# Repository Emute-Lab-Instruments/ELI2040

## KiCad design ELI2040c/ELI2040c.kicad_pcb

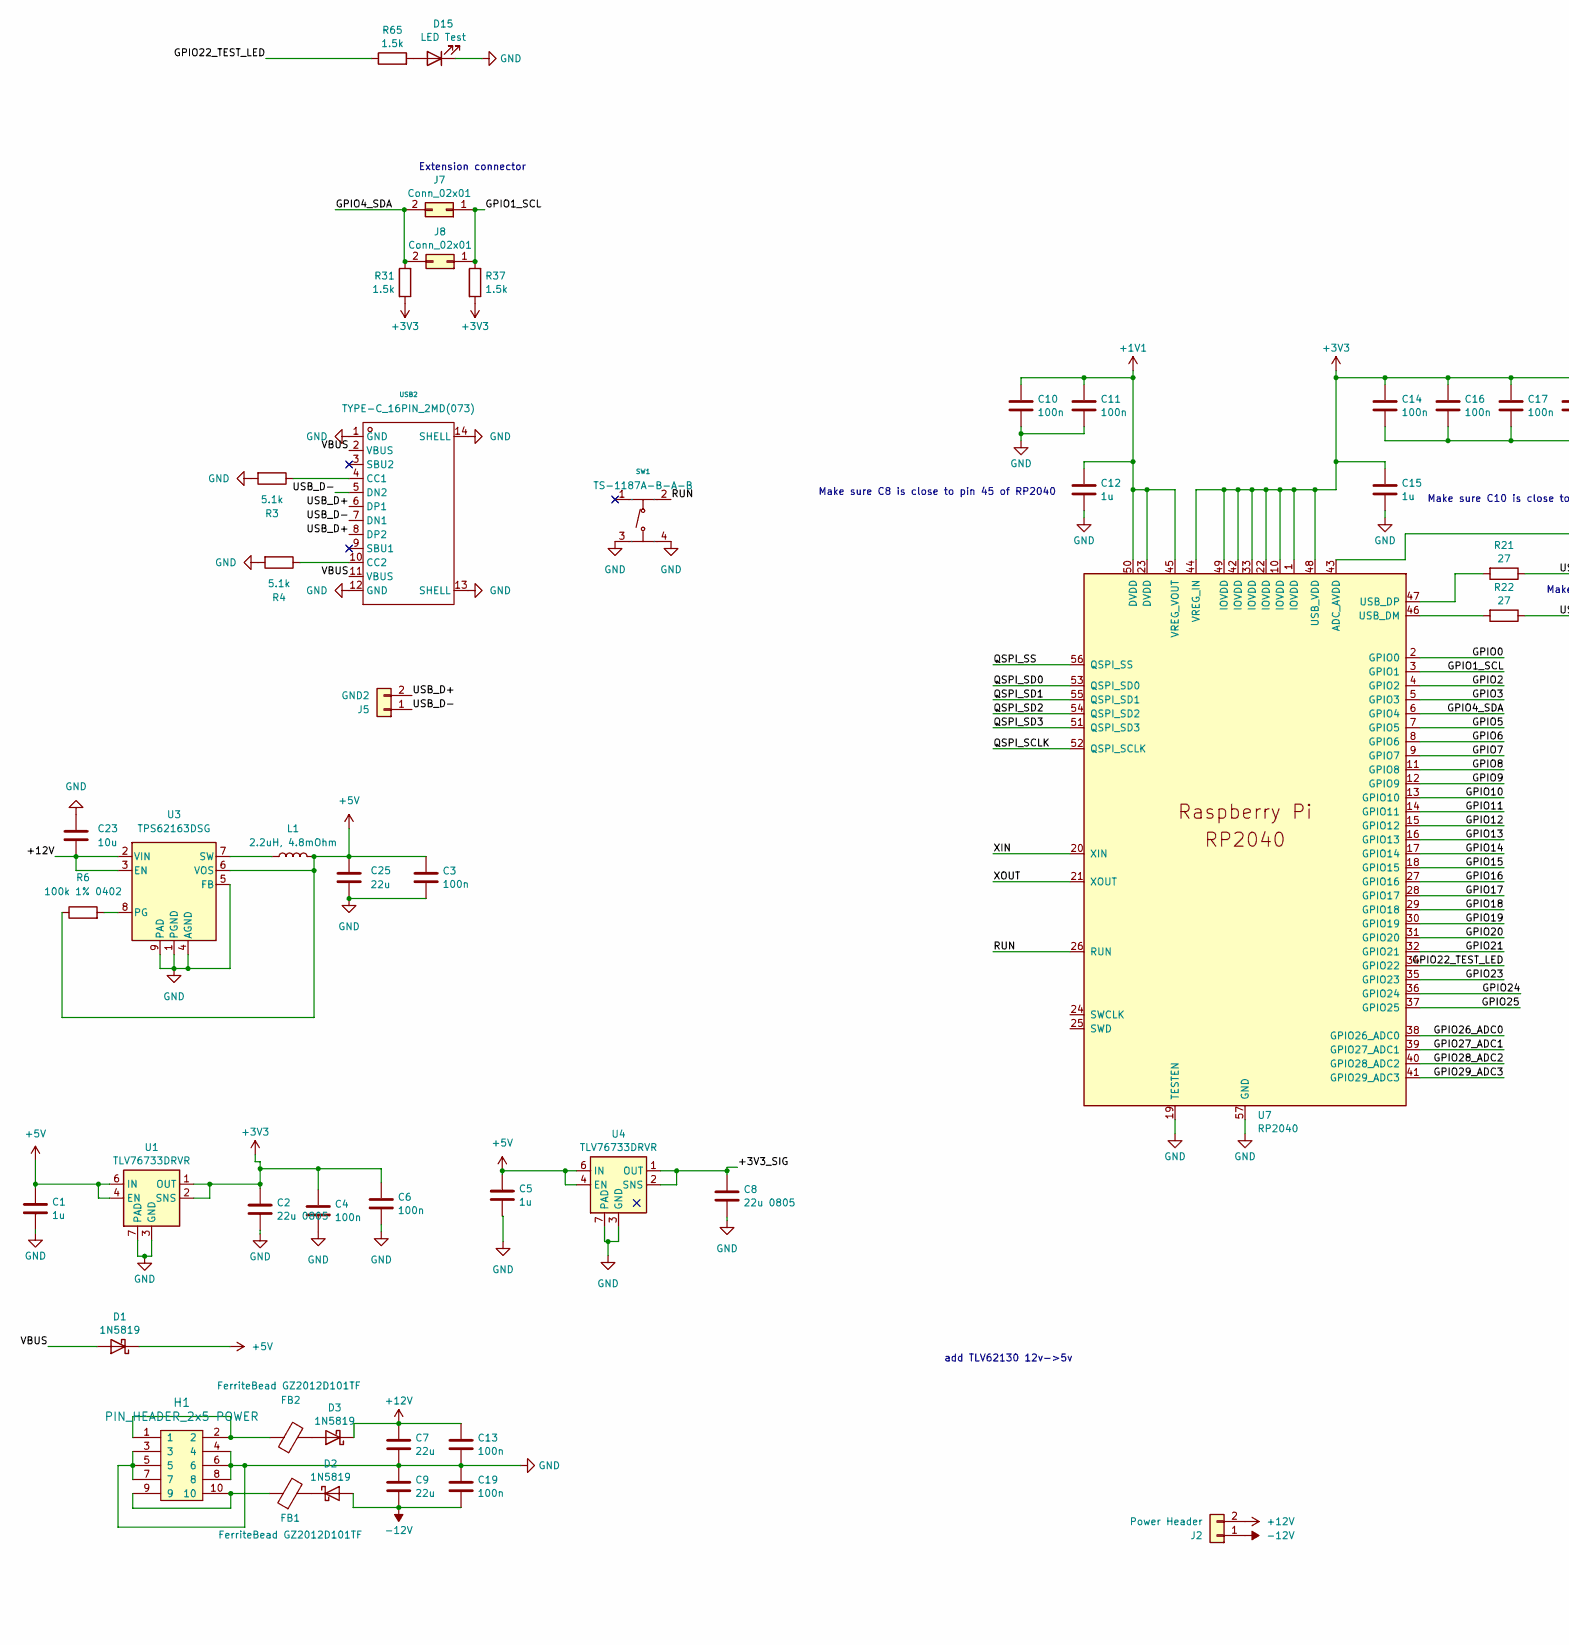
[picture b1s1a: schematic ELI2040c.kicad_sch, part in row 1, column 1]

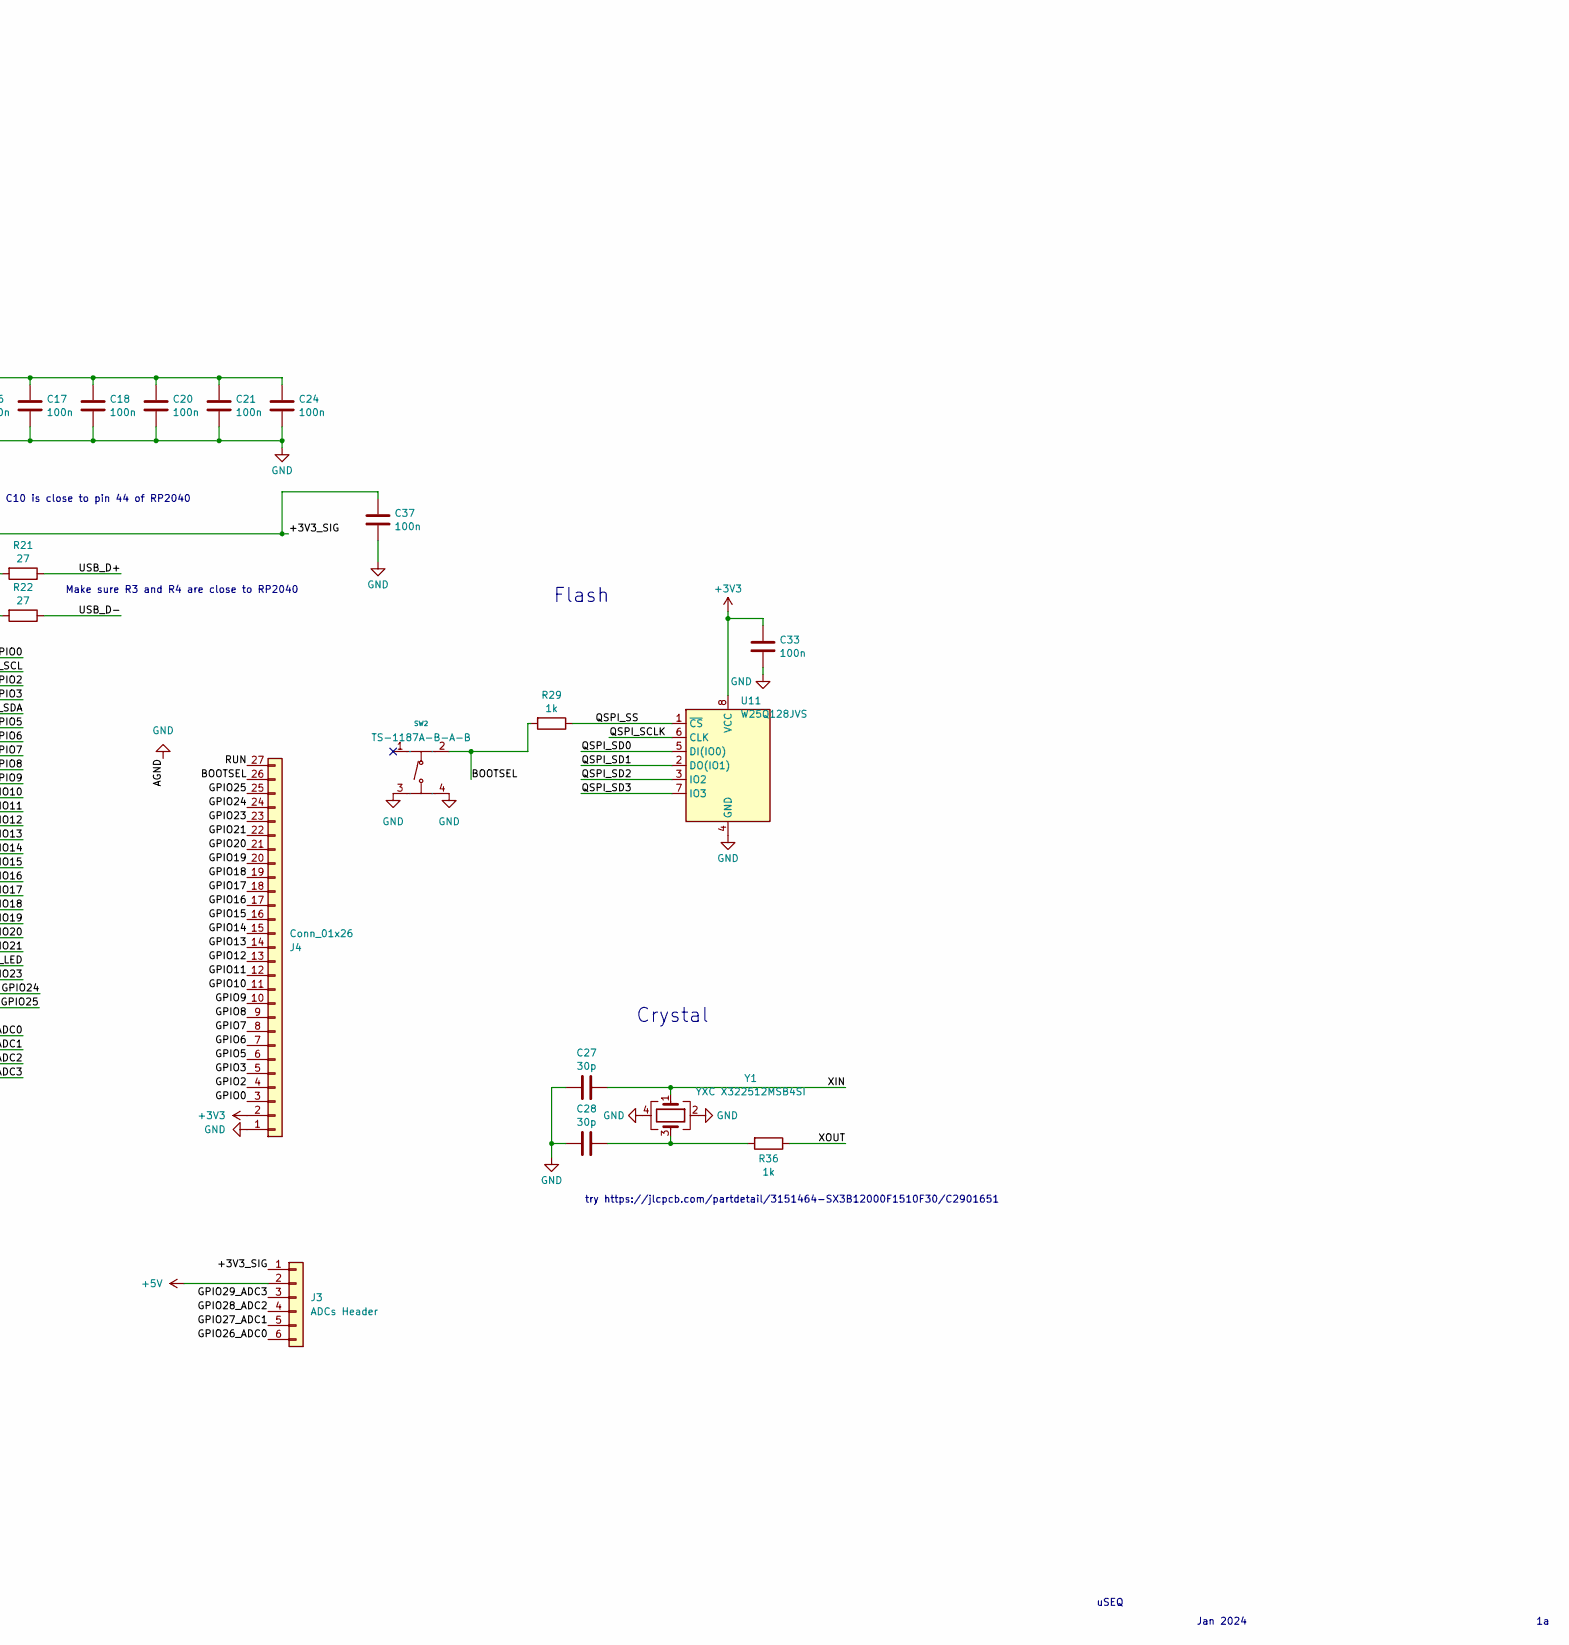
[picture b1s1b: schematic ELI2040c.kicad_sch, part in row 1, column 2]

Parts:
C1, C5: 1u; C_0603_1608Metric_Pad1.08x0.95mm_HandSolder
C2, C8: 22u 0805; C_0805_2012Metric_Pad1.18x1.45mm_HandSolder
C3, C13, C19: 100n; C_0603_1608Metric
C4, C6, C10, C11, C14, C16, C17, C18, C20, C21, C24, C33, C37: 100n; C_0402_1005Metric
C7, C9, C25: 22u; C_0805_2012Metric
C12, C15: 1u; C_0402_1005Metric
C23: 10u; C_0603_1608Metric
C27, C28: 30p; C_0402_1005Metric
D1, D2, D3: 1N5819; D_SOD-323
D15: LED Test; LED_0603_1608Metric
FB1, FB2: FerriteBead GZ2012D101TF; R_0805_2012Metric
H1: PIN_HEADER_2x5 POWER; PinHeader_2x05_P2.54mm_Vertical_SMD
J2: Power Header; PinHeader_1x02_P2.54mm_Vertical
J3: ADCs Header; PinHeader_1x06_P2.54mm_Vertical
J4: Conn_01x26; PinHeader_1x27_P2.54mm_Vertical
J5: GND2; PinHeader_1x02_P2.54mm_Vertical
J7, J8: Conn_02x01; PinHeader_1x02_P2.54mm_Vertical
L1: 2.2uH, 4.8mOhm; L_Sunlord_SWPA4020S
R3, R4: 5.1k; R_0402_1005Metric
R6: 100k 1% 0402; R_0402_1005Metric
R21, R22: 27; C_0402_1005Metric
R29: 1k; R_0402_1005Metric
R31, R37, R65: 1.5k; R_0603_1608Metric
R36: 1k; R_0603_1608Metric
SW1, SW2: TS-1187A-B-A-B; SW-SMD_4P-L5.1-W5.1-P3.70-LS6.5-TL-2; Manufacturer Part TS-1187A-B-A-B; LCSC Part Name 5.1*5.1*1.5mm 立贴 轻触开关
U1, U4: TLV76733DRVR; WSON-6-1EP_2x2mm_P0.65mm_EP1x1.6mm_ThermalVias
U3: TPS62163DSG; WSON-8-1EP_2x2mm_P0.5mm_EP0.9x1.6mm_ThermalVias
U7: RP2040; RP2040-QFN-56
U11: W25Q128JVS; SOIC-8_5.23x5.23mm_P1.27mm
USB2: TYPE-C_16PIN_2MD(073); USB-C-SMD_TYPE-C-6PIN-2MD-073
Y1: YXC X322512MSB4SI; Crystal_SMD_3225-4Pin_3.2x2.5mm

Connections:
+1V1: C10.1, C11.1, C12.1, U7.23 (DVDD), U7.45 (VREG_VOUT), U7.50 (DVDD)
+3V3: C2.1, C4.1, C6.1, C14.1, C15.1, C16.1, C17.1, C18.1, C20.1, C21.1, C24.1, C33.1, J4.2, R31.2, R37.2, U1.1 (OUT), U1.2 (SNS), U7.1 (IOVDD), U7.10 (IOVDD), U7.22 (IOVDD), U7.33 (IOVDD), U7.42 (IOVDD), U7.44 (VREG_IN), U7.48 (USB_VDD), U7.49 (IOVDD), U11.8 (VCC)
+5V: C1.1, C3.1, C5.1, C25.1, D1.1 (K), J3.2, L1.2, R6.1, U1.4 (EN), U1.6 (IN), U3.6 (VOS), U4.4 (EN), U4.6 (IN)
+12V: C7.1, C13.1, C23.2, D3.1 (K), J2.2, U3.2 (VIN), U3.3 (EN)
-12V: C9.2, C19.2, D2.2 (A), J2.1
/+3V3_SIG: C8.1, C37.1, J3.1, U4.1 (OUT), U4.2 (SNS), U7.43 (ADC_AVDD)
/BOOTSEL: J4.26, R29.2, SW2.2 (B)
/GPIO0: J4.3, U7.2 (GPIO0)
/GPIO1_SCL: J7.1, J8.1, R37.1, U7.3 (GPIO1)
/GPIO2: J4.4, U7.4 (GPIO2)
/GPIO3: J4.5, U7.5 (GPIO3)
/GPIO4_SDA: J7.2, J8.2, R31.1, U7.6 (GPIO4)
/GPIO5: J4.6, U7.7 (GPIO5)
/GPIO6: J4.7, U7.8 (GPIO6)
/GPIO7: J4.8, U7.9 (GPIO7)
/GPIO8: J4.9, U7.11 (GPIO8)
/GPIO9: J4.10, U7.12 (GPIO9)
/GPIO10: J4.11, U7.13 (GPIO10)
/GPIO11: J4.12, U7.14 (GPIO11)
/GPIO12: J4.13, U7.15 (GPIO12)
/GPIO13: J4.14, U7.16 (GPIO13)
/GPIO14: J4.15, U7.17 (GPIO14)
/GPIO15: J4.16, U7.18 (GPIO15)
/GPIO16: J4.17, U7.27 (GPIO16)
/GPIO17: J4.18, U7.28 (GPIO17)
/GPIO18: J4.19, U7.29 (GPIO18)
/GPIO19: J4.20, U7.30 (GPIO19)
/GPIO20: J4.21, U7.31 (GPIO20)
/GPIO21: J4.22, U7.32 (GPIO21)
/GPIO22_TEST_LED: R65.1, U7.34 (GPIO22)
/GPIO23: J4.23, U7.35 (GPIO23)
/GPIO24: J4.24, U7.36 (GPIO24)
/GPIO25: J4.25, U7.37 (GPIO25)
/GPIO26_ADC0: J3.6, U7.38 (GPIO26_ADC0)
/GPIO27_ADC1: J3.5, U7.39 (GPIO27_ADC1)
/GPIO28_ADC2: J3.4, U7.40 (GPIO28_ADC2)
/GPIO29_ADC3: J3.3, U7.41 (GPIO29_ADC3)
/QSPI_SCLK: U7.52 (QSPI_SCLK), U11.6 (CLK)
/QSPI_SD0: U7.53 (QSPI_SD0), U11.5 (DI(IO0))
/QSPI_SD1: U7.55 (QSPI_SD1), U11.2 (DO(IO1))
/QSPI_SD2: U7.54 (QSPI_SD2), U11.3 (IO2)
/QSPI_SD3: U7.51 (QSPI_SD3), U11.7 (IO3)
/QSPI_SS: R29.1, U7.56 (QSPI_SS), U11.1 (~CS)
/RUN: J4.27, SW1.2 (B), U7.26 (RUN)
/USB_D+: J5.2, R21.1, USB2.6 (DP1), USB2.8 (DP2)
/USB_D-: J5.1, R22.1, USB2.5 (DN2), USB2.7 (DN1)
/VBUS: D1.2 (A), USB2.2 (VBUS), USB2.11 (VBUS)
/XIN: C27.1, U7.20 (XIN), Y1.1
/XOUT: R36.1, U7.21 (XOUT)
GND: C1.2, C2.2, C3.2, C4.2, C5.2, C6.2, C7.2, C8.2, C9.1, C10.2, C11.2, C12.2, C13.2, C14.2, C15.2, C16.2, C17.2, C18.2, C19.1, C20.2, C21.2, C23.1, C24.2, C25.2, C27.2, C28.2, C33.2, C37.2, D15.1 (K), H1.3, H1.4, H1.5, H1.6, H1.7, H1.8, J4.1, R3.2, R4.2, SW1.3 (C), SW1.4 (D), SW2.3 (C), SW2.4 (D), U1.3 (GND), U1.5 (GND), U1.7 (PAD), U3.1 (PGND), U3.4 (AGND), U3.5 (FB), U3.9 (PAD), U4.3 (GND), U4.5 (GND), U4.7 (PAD), U7.19 (TESTEN), U7.57 (GND), U11.4 (GND), USB2.1 (GND), USB2.12 (GND), USB2.13 (SHELL), USB2.14 (SHELL), Y1.2, Y1.4
unnamed: C28.1, R36.2, Y1.3
unnamed: D2.1 (K), FB1.2
unnamed: D3.2 (A), FB2.2
unnamed: D15.2 (A), R65.2
unnamed: FB1.1, H1.9, H1.10
unnamed: FB2.1, H1.1, H1.2
unnamed: R6.2, U3.8 (PG)
unnamed: L1.1, U3.7 (SW)
unnamed: R22.2, U7.46 (USB_DM)
unnamed: R21.2, U7.47 (USB_DP)
unnamed: R3.1, USB2.4 (CC1)
unnamed: R4.1, USB2.10 (CC2)

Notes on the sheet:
Crystal
Extension connector
Make sure R3 and R4 are close to RP2040
add TLV62130 12v->5v
Flash
Make sure C10 is close to pin 44 of RP2040
Make sure C8 is close to pin 45 of RP2040
try https://jlcpcb.com/partdetail/3151464-SX3B12000F1510F30/C2901651
Jan 2024
uSEQ

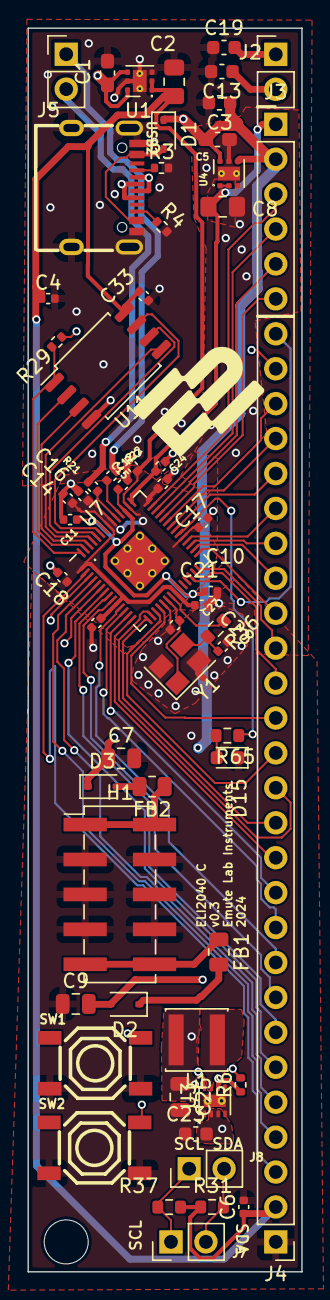
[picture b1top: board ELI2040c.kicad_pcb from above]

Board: 4 copper layers, 19.9 x 90.4 mm, 61 parts (0 on the bottom side), 62 nets.

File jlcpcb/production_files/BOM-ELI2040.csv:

Comment,Designator,Footprint,LCSC
27,"R21,R22",C_0402_1005Metric,C100353
30p,"C27,C28",C_0402_1005Metric,C107004
1k,R29,R_0402_1005Metric,C11702
1u,"C1,C5",C_0603_1608Metric_Pad1.08x0.95mm_HandSolder,C15849
1N5819,"D1,D4",D_SOD-323,C191023
RP2040,U7,RP2040-QFN-56,C2040
1k,R36,R_0603_1608Metric,C21190
1.5k,"R31,R37,R65",R_0603_1608Metric,C22843
LED Test,D15,LED_0603_1608Metric,C2286
5.1k,"R3,R4",R_0402_1005Metric,C25905
TYPE-C_16PIN_2MD(073),USB2,USB-C-SMD_TYPE-C-6PIN-2MD-073,C2765186
TLV76733DRVR,"U1,U4",WSON-6-1EP_2x2mm_P0.65mm_EP1x1.6mm_ThermalVias,C2848334
100n,"C10,C11,C14,C16,C17,C18,C20,C21,C24,C33,C37,C4,C6",C_0402_1005Metric,C307331
TS-1187A-B-A-B,"SW1,SW2",SW-SMD_4P-L5.1-W5.1-P3.70-LS6.5-TL-2,C318884
22u 0805 ,"C2,C3,C8",C_0805_2012Metric_Pad1.18x1.45mm_HandSolder,C45783
1u,"C12,C15",C_0402_1005Metric,C52923
YXC X322512MSB4SI,Y1,Crystal_SMD_3225-4Pin_3.2x2.5mm,C9002
W25Q128JVS,U11,SOIC-8_5.23x5.23mm_P1.27mm,C97521

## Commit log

2024-07-04 innit
2024-07-05 update 2
2024-07-05 update 3
2024-08-13 latest v0.1
2024-12-11 reorg
2024-12-11 ignore
2024-12-11 versions
2024-12-11 reoorg
